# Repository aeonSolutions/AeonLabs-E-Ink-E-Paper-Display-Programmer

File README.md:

[PCB-Prototyping-Catalogue](https://github.com/aeonSolutions/PCB-Prototyping-Catalogue)  >>  [Smart LCD Touch Displays](https://github.com/aeonSolutions/PCB-Prototyping-Catalogue/tree/main/Smart%20LCD%20Touch%20Displays)  >>  E-Ink / E-Paper Display Programmer

<br>

# E-Ink / E-Paper Display Programmer
This repo contains the KiCad files for the AeonLabs E-Ink / E-Paper Display Programmer. This PCB can program any E-Ink Displays with a 24 pin FPC/FFC connector.
It can fit an enclosure with dimensions of 35x35x4 mm

*Don't forget to LIKE , SHARE and subscribe the free whatsApp group* and if you liked this PCB consider buying me a cup of coffee. Links below.

### Status
  Waiting for first batch from factory. Not tested.

If you already tested this PCB send me a message. Thank you

## Revisions
- revision 2.0 (ToDo)
  - Android & Desktop Apps
  -  
- revision 1.0
  - Information / Image programmer for E-Ink / E-paper Display  
 
## Download options
Download this repository if you need the KiCad Files or, download the Gerber files in the release section of this repository

## Liked it ? Get a Free PCB for yourself
Send me your Device or hardware and i will design a custom PCB for it. Free of charge. Contact-me on WhatsApp or email for more info. 

## Q&A WhatsApp Group
If you have any Questions or simply  like this kind of projects and want to stay updated with the latest research ideas and prototypes during the day and week, join the WhatsApp Group
[LDAD Lab & Prototyping](https://chat.whatsapp.com/FkNC7u83kuy2QRA5sqjBVg)

## Fully assembled PCB
### alternatively, and if you do not want to build a PCB by yourself, you can buy here:

The price will be around 30eur plus postage fees.
(I will also deliver the assembled PCB with all the components in place at a fair aditonal cost).
#### Be supportive of my dedication and work towards technology education and buy me a coffee. Link below.

________________________________________________________________________________________________________________
## [Go back to main catalogue page](https://github.com/aeonSolutions/PCB-Prototyping-Catalogue)
________________________________________________________________________________________________________________

## PCB Parts list
- DC2DC converter HX4002B x2 : https://s.click.aliexpress.com/e/_Ak7IPx
- Capacitor 100nF SMD 1206 : https://s.click.aliexpress.com/e/_AVdmzr
- Capacitor 2.2uF SMD 1206 : https://s.click.aliexpress.com/e/_AVdmzr
- LED SMD 1206 : https://s.click.aliexpress.com/e/_A9THIl
- Resistor SMD 1206 330R : https://s.click.aliexpress.com/e/_A7OXrR
- Micro USB PCB socket : https://s.click.aliexpress.com/e/_A123KH 

<br />
<br />

______________________________________________________________________________________________________________________________

### PCB Conceptualization and Design
<p align="center">

</p>

<br />
<br />

### PCB Fabrication
<p align="center">

</p>

<br />
<br />

## Author

You can get in touch with me on my LinkedIn Profile:

#### Miguel Tomas

You can also follow my GitHub Profile to stay updated about my latest projects: 

<br>

### Be supportive of my dedication and work towards technology education and buy me a cup of coffee
The PCB Desgin Files i provide here for anyone to use are free. If you like this Smart Device or use it, please consider buying me a cup of coffee, a slice of pizza or a book to help me study, eat and think new PCB design files.

<p align+"left">

<br>

</p>

<br />

### Make a donation on Paypal
Make a donation on paypal and get a TAX refund*.

<br>

### Support all these open hardware projects and become a patreon  
Liked any of my PCB KiCad Designs? Help and Support my open work to all by becomming a LDAD Patreon.
In return I will give a free PCB design in KiCad to all patreon supporters. To learn more go to patreon.com. Link below.

<br />
<br />

______________________________________________________________________________________________________________________________
### License

Before proceeding to download any of AeonLabs software solutions for open-source development and/or PCB hardware electronics development make sure you are choosing the right license for your project. See [AeonLabs Solutions for Open Hardware & Source Development](https://github.com/aeonSolutions/PCB-Prototyping-Catalogue/wiki/AeonLabs-Solutions-for-Open-Hardware-&-Source-Development) for more information. 

______________________________________________________________________________________________________________________________

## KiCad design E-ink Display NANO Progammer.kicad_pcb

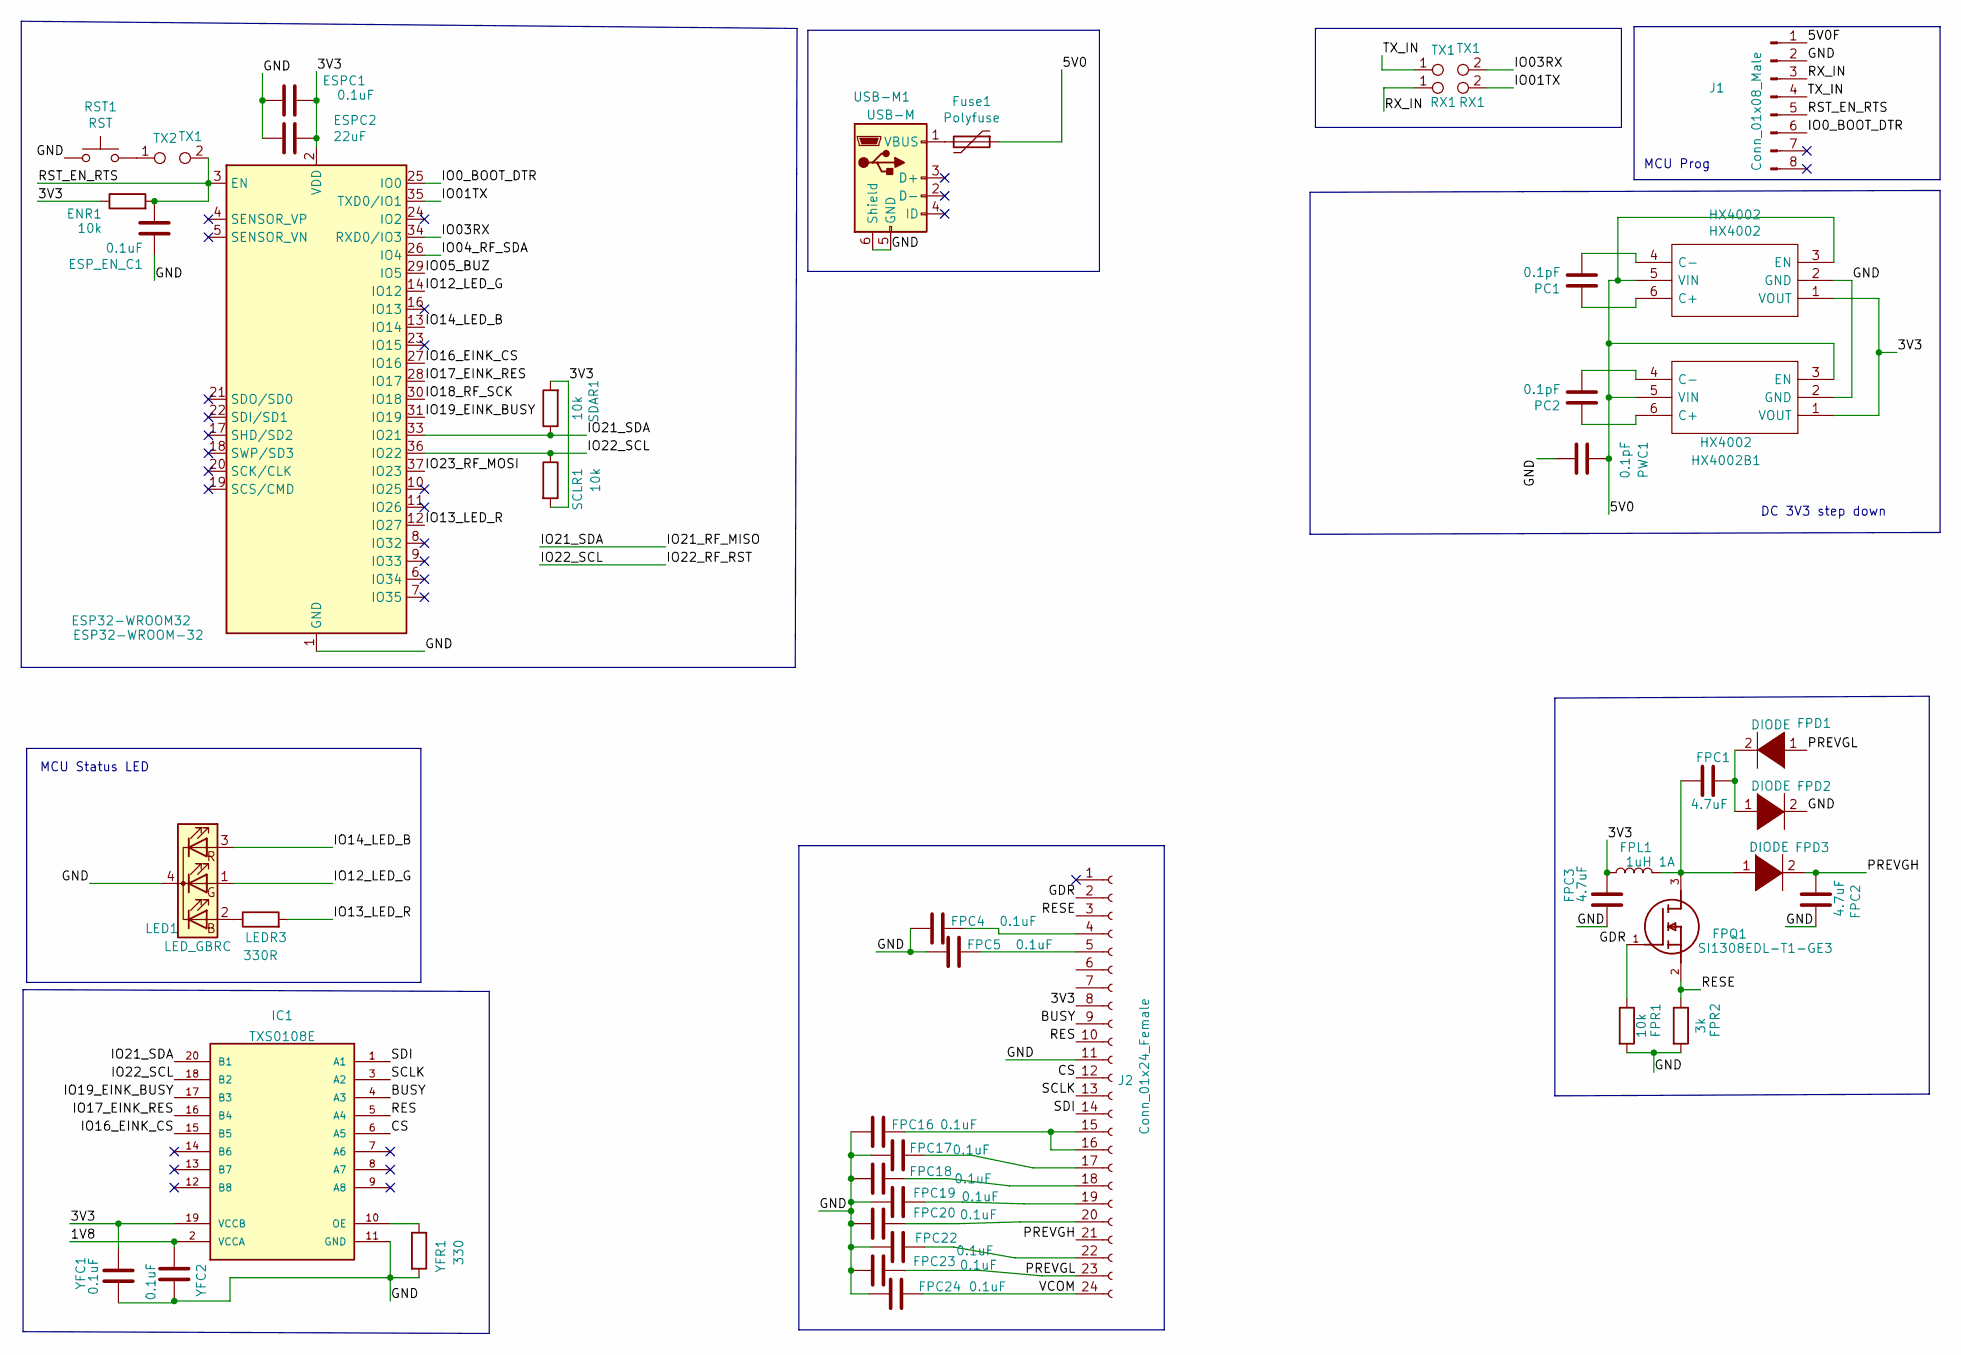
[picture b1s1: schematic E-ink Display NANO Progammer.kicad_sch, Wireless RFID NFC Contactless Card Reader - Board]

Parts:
ENR1: 10k; R_1206_3216MetricTrue
ESP32-WROOM32: ESP32-WROOM-32
ESPC1: 0.1uF; C_1206_3216MetricTrue
ESPC2: 22uF; C_1206_3216MetricTrue
ESP_EN_C1: 0.1uF; C_1206_3216MetricTrue
FPC1, FPC2, FPC3: 4.7uF; C_1206_3216MetricTrue
FPC4, FPC5, FPC16, FPC17, FPC18, FPC19, FPC20, FPC22, FPC23, FPC24: 0.1uF; C_1206_3216MetricTrue
FPD1, FPD2, FPD3: DIODE; C_1206_3216MetricTrue
FPL1: 1uH 1A; C_1206_3216MetricTrue
FPQ1: SI1308EDL-T1-GE3; SI1308EDL-T1-GE3_SOT65P210X110-3N; Mouser_Part_Number 78-SI1308EDL-T1-GE3
FPR1: 10k; R_1206_3216MetricTrue
FPR2: 3k; R_1206_3216MetricTrue
Fuse1: Polyfuse; Fuse_1206_3216Metric_Pad1.42x1.75mm_HandSolder
HX4002, HX4002B1: HX4002; HX4002 SOT95 P280X125-6N; Manufacturer_Part_Number HX4002
IC1: TXS0108E; TXS0108E_YF08E_PW_R-PDSO-G20
J1: Conn_01x08_Male; SOIC_clipProgSmall
J2: Conn_01x24_Female; Hirose_FH12-24S-0.5SH_1x24-1MP_P0.50mm_Horizontal
LED1: LED_GBRC; LED_1206_3210_RGB_Metric
LEDR3: 330R; R_1206_3216MetricTrue
PC1, PC2: 0.1pF; C_1206_3216MetricTrue
PWC1: 0.1pF; C_1206_3216MetricTrue
RST1: RST; SW_Push_SPST_NO_Alps_SKRK AliExpress
RX1: RX1; TestPoint_Pad_Bridge_1.0x1.0mm
SCLR1: 10k; R_1206_3216MetricTrue
SDAR1: 10k; R_1206_3216MetricTrue
TX1, TX2: TX1; TestPoint_Pad_Bridge_1.0x1.0mm
USB-M1: USB-M; Micro_USB_pcb_socket_5pin_4weld_points
YFC1, YFC2: 0.1uF; C_1206_3216MetricTrue
YFR1: 330; R_1206_3216MetricTrue

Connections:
/1V8: IC1.2 (VCCA), YFC2.1
/3V3: ENR1.1, ESP32-WROOM32.2 (VDD), ESPC1.1, ESPC2.1, FPC3.1, FPL1.1, HX4002.1 (VOUT), HX4002B1.1 (VOUT), IC1.19 (VCCB), J2.8, SCLR1.2, SDAR1.2, YFC1.1
/5V0: Fuse1.1, HX4002.3 (EN), HX4002.5 (VIN), HX4002B1.3 (EN), HX4002B1.5 (VIN), PWC1.1
/5V0F: J1.1
/BUSY: IC1.4 (A3), J2.9
/CS: IC1.6 (A5), J2.12
/GDR: FPQ1.1, FPR1.1, J2.2
/GND: ESP32-WROOM32.1 (GND), ESP32-WROOM32.15 (GND), ESP32-WROOM32.38 (GND), ESP32-WROOM32.39 (GND), ESPC1.2, ESPC2.2, ESP_EN_C1.1, FPC2.2, FPC3.2, FPC4.2, FPC5.2, FPC16.2, FPC17.2, FPC18.2, FPC19.2, FPC20.2, FPC22.2, FPC23.2, FPC24.2, FPD2.2 (A), FPR1.2, FPR2.2, HX4002.2 (GND), HX4002B1.2 (GND), IC1.11 (GND), J1.2, J2.11, LED1.4 (K), PWC1.2, RST1.1, USB-M1.5 (GND), USB-M1.6 (Shield), YFC1.2, YFC2.2, YFR1.2
/IO0_BOOT_DTR: ESP32-WROOM32.25 (IO0), J1.6
/IO01TX: ESP32-WROOM32.35 (TXD0/IO1), RX1.2
/IO03RX: ESP32-WROOM32.34 (RXD0/IO3), TX1.2
/IO04_RF_SDA: ESP32-WROOM32.26 (IO4)
/IO05_BUZ: ESP32-WROOM32.29 (IO5)
/IO12_LED_G: ESP32-WROOM32.14 (IO12), LED1.1 (GA)
/IO13_LED_R: ESP32-WROOM32.12 (IO27), LEDR3.2
/IO14_LED_B: ESP32-WROOM32.13 (IO14), LED1.3 (RA)
/IO16_EINK_CS: ESP32-WROOM32.27 (IO16), IC1.15 (B5)
/IO17_EINK_RES: ESP32-WROOM32.28 (IO17), IC1.16 (B4)
/IO18_RF_SCK: ESP32-WROOM32.30 (IO18)
/IO19_EINK_BUSY: ESP32-WROOM32.31 (IO19), IC1.17 (B3)
/IO21_RF_MISO: ESP32-WROOM32.33 (IO21), IC1.20 (B1), SDAR1.1
/IO22_RF_RST: ESP32-WROOM32.36 (IO22), IC1.18 (B2), SCLR1.1
/IO23_RF_MOSI: ESP32-WROOM32.37 (IO23)
/PREVGH: FPC2.1, FPD3.2 (A), J2.21
/PREVGL: FPC23.1, FPD1.1 (K), J2.23
/RES: IC1.5 (A4), J2.10
/RESE: FPQ1.2, FPR2.1, J2.3
/RST_EN_RTS: ENR1.2, ESP32-WROOM32.3 (EN), ESP_EN_C1.2, J1.5, TX2.2
/RX_IN: J1.3, RX1.1
/SCLK: IC1.3 (A2), J2.13
/SDI: IC1.1 (A1), J2.14
/TX_IN: J1.4, TX1.1
/VCOM: FPC24.1, J2.24
unnamed: FPC1.1, FPD1.2 (A), FPD2.1 (K)
unnamed: FPC1.2, FPD3.1 (K), FPL1.2, FPQ1.3
unnamed: FPC4.1, J2.4
unnamed: FPC5.1, J2.5
unnamed: FPC16.1, J2.15, J2.16
unnamed: FPC17.1, J2.17
unnamed: FPC18.1, J2.18
unnamed: FPC19.1, J2.19
unnamed: FPC20.1, J2.20
unnamed: FPC22.1, J2.22
unnamed: Fuse1.2, USB-M1.1 (VBUS)
unnamed: HX4002.4 (C-), PC1.2
unnamed: HX4002.6 (C+), PC1.1
unnamed: HX4002B1.4 (C-), PC2.2
unnamed: HX4002B1.6 (C+), PC2.1
unnamed: IC1.10 (OE), YFR1.1
unnamed: LED1.2 (BA), LEDR3.1
unnamed: RST1.2, TX2.1

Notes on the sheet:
DC 3V3 step down
MCU Prog
MCU Status LED

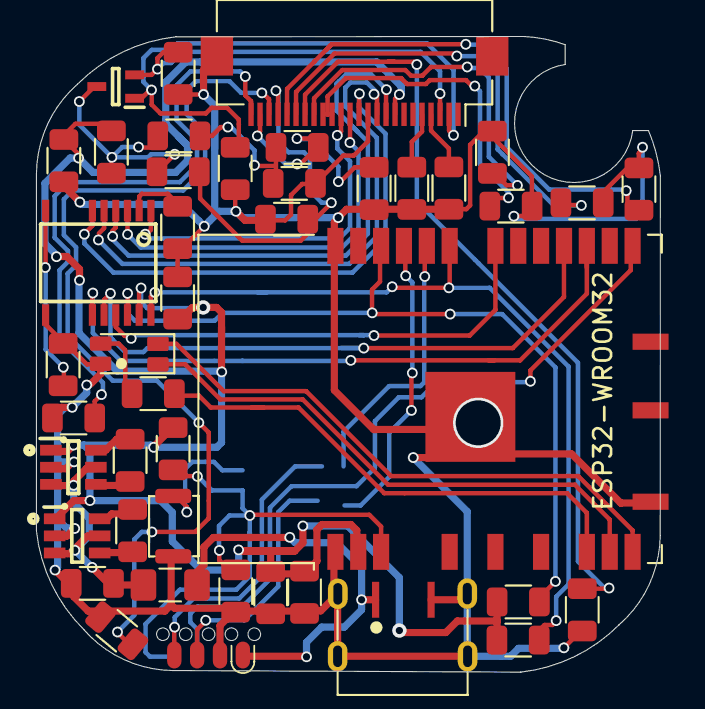
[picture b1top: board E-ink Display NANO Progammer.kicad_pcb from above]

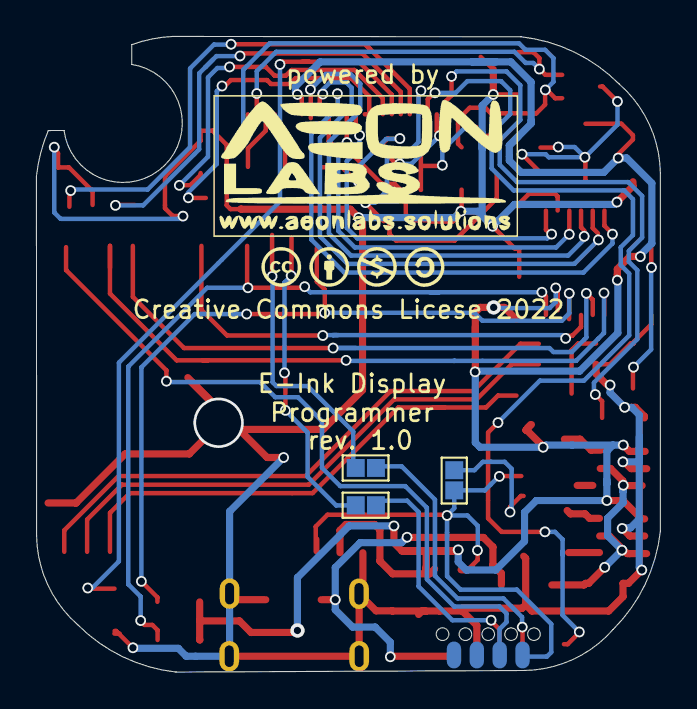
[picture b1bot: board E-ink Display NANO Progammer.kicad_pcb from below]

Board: 2 copper layers, 34.7 x 35.3 mm, 46 parts (3 on the bottom side), 46 nets.

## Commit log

2022-05-26 rev 1.0

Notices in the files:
E-ink Display NANO Progammer.kicad_pcb:
Copyright 2022
Creative Commons Licese 2022
